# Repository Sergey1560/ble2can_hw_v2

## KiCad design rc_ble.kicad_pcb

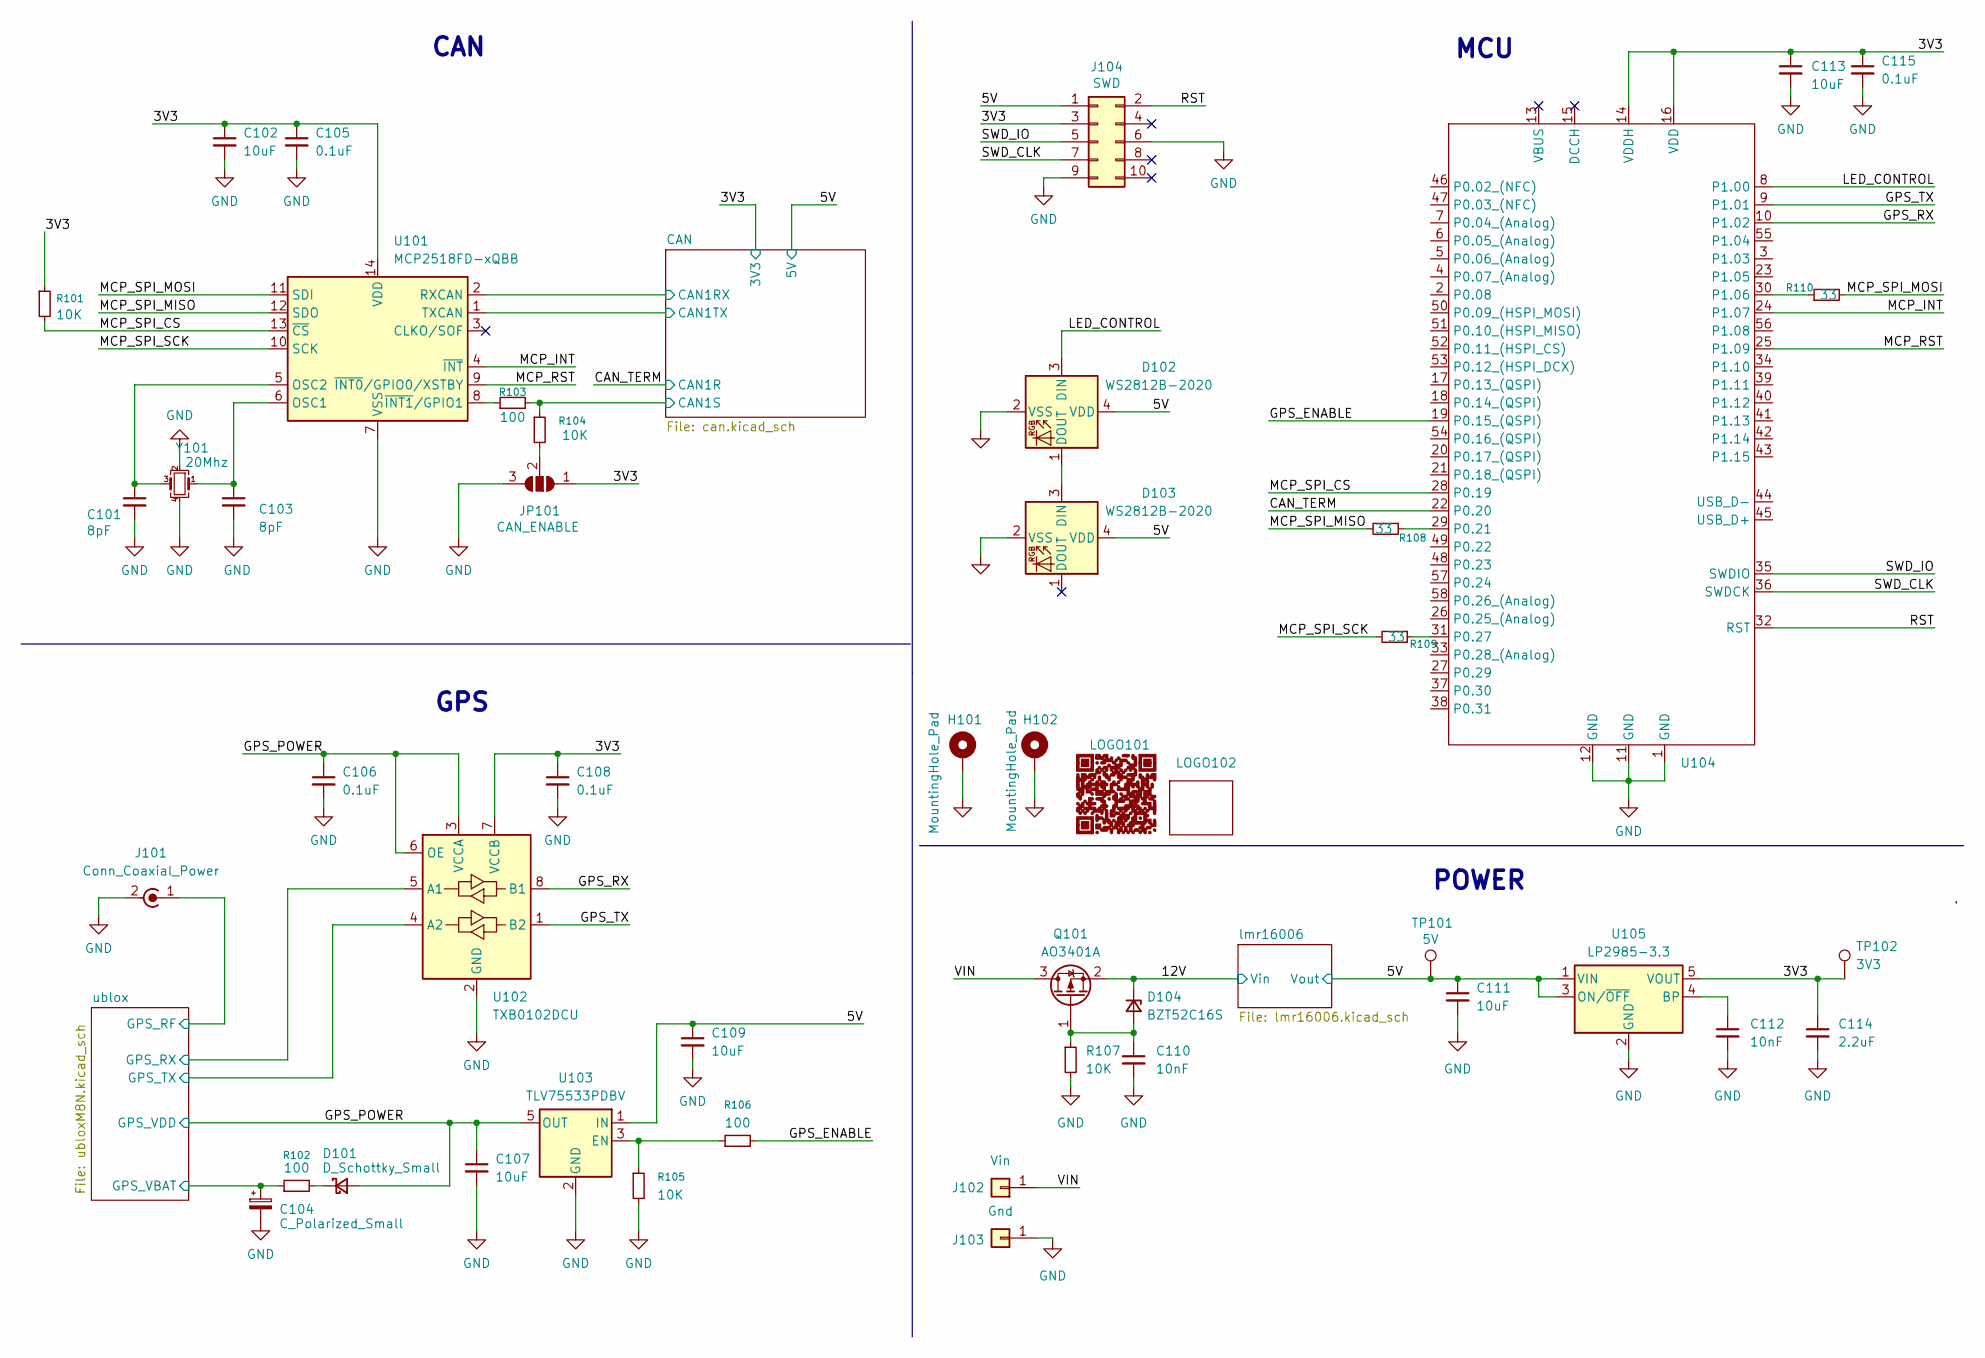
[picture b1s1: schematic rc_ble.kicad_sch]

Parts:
C101, C103: 8pF; C_0603_1608Metric; LCSC C38523
C102, C107, C109, C113: 10uF; C_0805_2012Metric
C104: C_Polarized_Small; CP_Radial_D8.0mm_P3.50mm
C105, C115: 0.1uF; C_0603_1608Metric
C106, C108: 0.1uF; C_0603_1608Metric; LCSC C14663
C110, C112: 10nF; C_0603_1608Metric; LCSC C57112
C111: 10uF; C_0603_1608Metric; LCSC C15849
C114: 2.2uF; C_0603_1608Metric; LCSC C23630
D101: D_Schottky_Small; D_SOD-323_HandSoldering
D102, D103: WS2812B-2020; LED_WS2812B-2020_PLCC4_2.0x2.0mm; LCSC C965555
D104: BZT52C16S; D_SOD-323_HandSoldering; LCSC C173447
H101, H102: MountingHole_Pad; MountingHole_2.2mm_M2_Pad_Via
J101: Conn_Coaxial_Power; SMA_Amphenol_132134_Vertical
J102: Vin; PinHeader_1x01_P2.54mm_Vertical
J103: Gnd; PinHeader_1x01_P2.54mm_Vertical
J104: SWD; PinHeader_2x05_P1.27mm_Vertical_SMD
JP101: CAN_ENABLE; SolderJumper-3_P1.3mm_Open_RoundedPad1.0x1.5mm
LOGO101: logo_github
LOGO102: logo_15x9
Q101: AO3401A; SOT-23; LCSC C15127
R101, R104, R105, R107: 10K; R_0603_1608Metric; LCSC C25804
R102, R103, R106: 100; R_0603_1608Metric
R108, R109, R110: 33; R_0603_1608Metric
TP101: 5V; TestPoint_Pad_1.0x1.0mm
TP102: 3V3; TestPoint_Pad_1.0x1.0mm
U101: MCP2518FD-xQBB; DFN-14-1EP_3x4.5mm_P0.65mm_EP1.65x4.25mm; LCSC C621395
U102: TXB0102DCU; VSSOP-8_2.3x2mm_P0.5mm; LCSC C60709
U103: TLV75533PDBV; SOT-23-5
U104: nrf5340
U105: LP2985-3.3; SOT-23-5; LCSC C95414
Y101: 20Mhz; Crystal_SMD_3225-4Pin_3.2x2.5mm

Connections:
/3V3: C102.1, C105.1, C108.1, C113.1, C114.1, C115.1, J104.3, JP101.1 (A), R101.1, TP102.1, U101.14 (VDD), U102.7 (VCCB), U104.14 (VDDH), U104.16 (VDD), U105.5 (VOUT); also elsewhere on the board
/5V: C109.1, C111.1, D102.4 (VDD), D103.4 (VDD), J104.1, TP101.1, U103.1 (IN), U105.1 (VIN), U105.3 (ON/~OFF); also elsewhere on the board
/12V: D104.1 (K), Q101.2 (S); also elsewhere on the board
/CAN/CAN1RX: U101.2 (RXCAN); also elsewhere on the board
/CAN/CAN1S: R103.2, R104.1; also elsewhere on the board
/CAN/CAN1TX: U101.1 (TXCAN); also elsewhere on the board
/CAN_TERM: U104.22 (P0.20); also elsewhere on the board
/GPS_ENABLE: R106.2, U104.19 (P0.15_(QSPI))
/GPS_POWER: C106.1, C107.1, D101.2 (A), U102.3 (VCCA), U102.6 (OE), U103.5 (OUT); also elsewhere on the board
/GPS_RX: U102.8 (B1), U104.10 (P1.02)
/GPS_TX: U102.1 (B2), U104.9 (P1.01)
/LED_CONTROL: D102.3 (DIN), U104.8 (P1.00)
/MCP_INT: U101.4 (~INT), U104.24 (P1.07)
/MCP_RST: U101.9 (~INT0/GPIO0/XSTBY), U104.25 (P1.09)
/MCP_SPI_CS: R101.2, U101.13 (~CS), U104.28 (P0.19)
/MCP_SPI_MISO: R108.2, U101.12 (SDO)
/MCP_SPI_MOSI: R110.2, U101.11 (SDI)
/MCP_SPI_SCK: R109.2, U101.10 (SCK)
/RST: J104.2, U104.32 (RST)
/SWD_CLK: J104.7, U104.36 (SWDCK)
/SWD_IO: J104.5, U104.35 (SWDIO)
/VIN: J102.1, Q101.3 (D)
/ublox/GPS_RF: J101.1 (In); also elsewhere on the board
/ublox/GPS_RX: U102.5 (A1); also elsewhere on the board
/ublox/GPS_TX: U102.4 (A2); also elsewhere on the board
/ublox/GPS_VBAT: C104.1, R102.1; also elsewhere on the board
GND: C101.2, C102.2, C103.2, C104.2, C105.2, C106.2, C107.2, C108.2, C109.2, C110.2, C111.2, C112.2, C113.2, C114.2, C115.2, D102.2 (VSS), D103.2 (VSS), H101.1, H102.1, J101.2 (Ext), J103.1, J104.6, J104.9, JP101.3 (B), R105.2, R107.2, U101.7 (VSS), U101.15 (VSS), U102.2 (GND), U103.2 (GND), U104.1 (GND), U104.11 (GND), U104.12 (GND), U105.2 (GND), Y101.2, Y101.4; also elsewhere on the board
unnamed: D101.1 (K), R102.2
unnamed: D102.1 (DOUT), D103.3 (DIN)
unnamed: C110.1, D104.2 (A), Q101.1 (G), R107.1
unnamed: JP101.2 (C), R104.2
unnamed: C103.1, U101.6 (OSC1), Y101.1
unnamed: C101.1, U101.5 (OSC2), Y101.3
unnamed: R103.1, U101.8 (~INT1/GPIO1)
unnamed: R105.1, R106.1, U103.3 (EN)
unnamed: R108.1, U104.29 (P0.21)
unnamed: R109.1, U104.31 (P0.27)
unnamed: R110.1, U104.30 (P1.06)
unnamed: C112.1, U105.4 (BP)

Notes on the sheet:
GPS
CAN
MCU
POWER

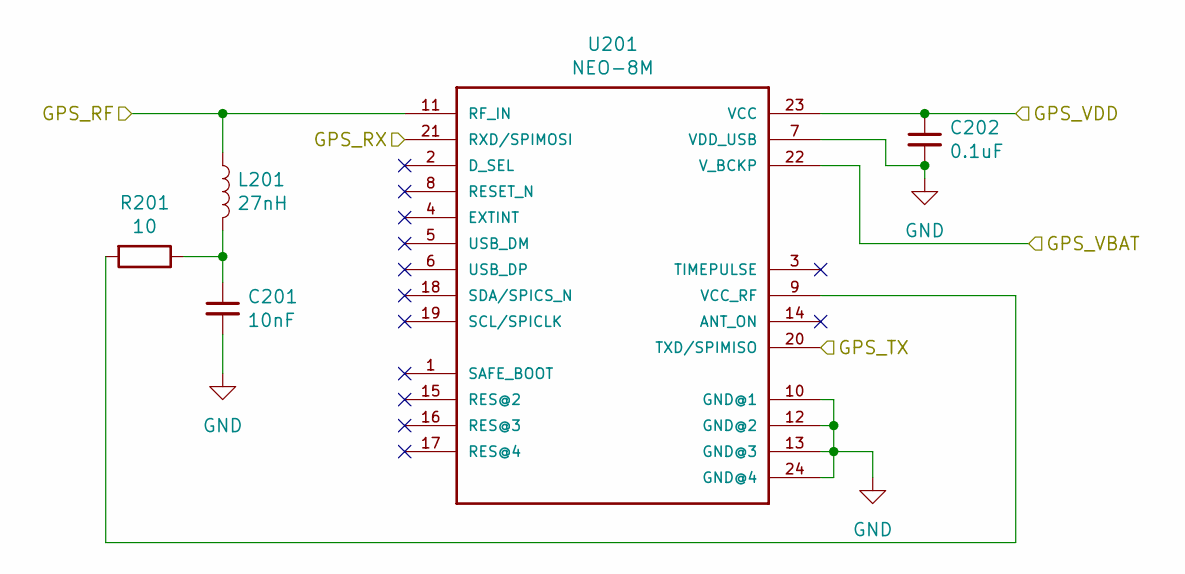
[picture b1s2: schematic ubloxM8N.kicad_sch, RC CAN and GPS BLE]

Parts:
C201: 10nF; C_0603_1608Metric
C202: 0.1uF; C_0805_2012Metric
L201: 27nH; L_0805_2012Metric
R201: 10; R_0603_1608Metric
U201: NEO-8M; ublox_NEO; LCSC C5119087

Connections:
/GPS_POWER: C202.1, U201.23 (VCC); also elsewhere on the board
/ublox/GPS_RF: L201.1, U201.11 (RF_IN); also elsewhere on the board
/ublox/GPS_RX: U201.21 (RXD/SPIMOSI); also elsewhere on the board
/ublox/GPS_TX: U201.20 (TXD/SPIMISO); also elsewhere on the board
/ublox/GPS_VBAT: U201.22 (V_BCKP); also elsewhere on the board
GND: C201.2, C202.2, U201.7 (VDD_USB), U201.10 (GND@1), U201.12 (GND@2), U201.13 (GND@3), U201.24 (GND@4); also elsewhere on the board
unnamed: C201.1, L201.2, R201.1
unnamed: R201.2, U201.9 (VCC_RF)

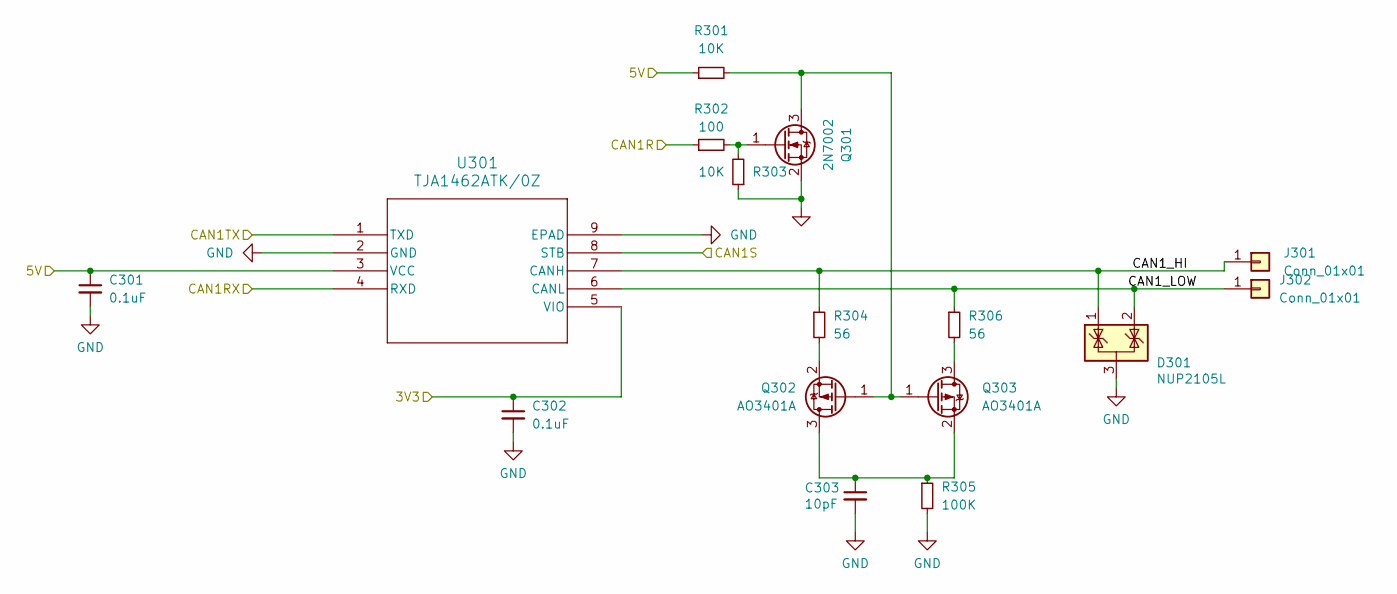
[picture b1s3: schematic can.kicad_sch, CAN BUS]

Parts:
C301, C302: 0.1uF; C_0603_1608Metric; LCSC C14663
C303: 10pF; C_0603_1608Metric; LCSC C1669
D301: NUP2105L; SOT-23; LCSC C284104
J301, J302: Conn_01x01; PinHeader_1x01_P2.54mm_Vertical
Q301: 2N7002; SOT-23; LCSC C8545
Q302, Q303: AO3401A; SOT-23; LCSC C15127
R301, R303: 10K; R_0603_1608Metric; LCSC C25804
R302: 100; R_0603_1608Metric; LCSC C22775
R304, R306: 56; R_0603_1608Metric; LCSC C25196
R305: 100K; R_0603_1608Metric; LCSC C25803
U301: TJA1462ATK/0Z; HVSON8_TJA1462_NXP; LCSC C3229259

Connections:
/3V3: C302.1, U301.5 (VIO); also elsewhere on the board
/5V: C301.1, R301.1, U301.3 (VCC); also elsewhere on the board
/CAN/CAN1RX: U301.4 (RXD); also elsewhere on the board
/CAN/CAN1S: U301.8 (STB); also elsewhere on the board
/CAN/CAN1TX: U301.1 (TXD); also elsewhere on the board
/CAN/CAN1_HI: D301.1 (K), J301.1, R304.1, U301.7 (CANH)
/CAN/CAN1_LOW: D301.2 (K), J302.1, R306.1, U301.6 (CANL)
/CAN_TERM: R302.1; also elsewhere on the board
GND: C301.2, C302.2, C303.2, D301.3 (A), Q301.2 (S), R303.1, R305.2, U301.2 (GND), U301.9 (EPAD); also elsewhere on the board
unnamed: Q301.3 (D), Q302.1 (G), Q303.1 (G), R301.2
unnamed: Q301.1 (G), R302.2, R303.2
unnamed: C303.1, Q302.3 (D), Q303.2 (S), R305.1
unnamed: Q302.2 (S), R304.2
unnamed: Q303.3 (D), R306.2

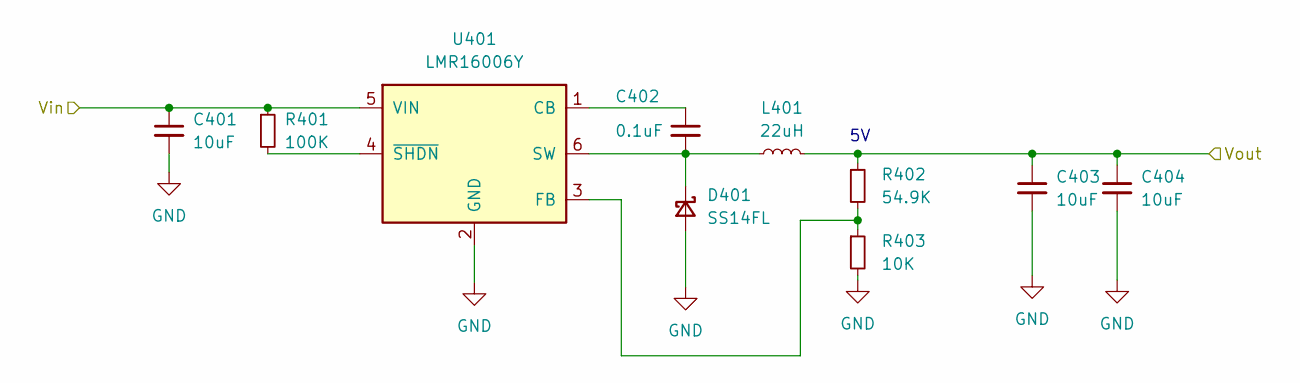
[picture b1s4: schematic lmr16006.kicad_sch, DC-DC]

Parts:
C401, C403, C404: 10uF; C_0805_2012Metric; LCSC C440198
C402: 0.1uF; C_0805_2012Metric; LCSC C28233
D401: SS14FL; D_SMA; LCSC C111580
L401: 22uH; FNR5040S220MT; LCSC C167971
R401: 100K; R_0603_1608Metric; LCSC C25803
R402: 54.9K; R_0603_1608Metric; LCSC C728593
R403: 10K; R_0603_1608Metric; LCSC C25804
U401: LMR16006Y; SOT-23-6; LCSC C290195

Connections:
/5V: C403.1, C404.1, L401.2, R402.1; also elsewhere on the board
/12V: C401.1, R401.1, U401.5 (VIN); also elsewhere on the board
GND: C401.2, C403.2, C404.2, D401.2 (A), R403.2, U401.2 (GND); also elsewhere on the board
unnamed: C402.2, D401.1 (K), L401.1, U401.6 (SW)
unnamed: C402.1, U401.1 (CB)
unnamed: R402.2, R403.1, U401.3 (FB)
unnamed: R401.2, U401.4 (~SHDN)

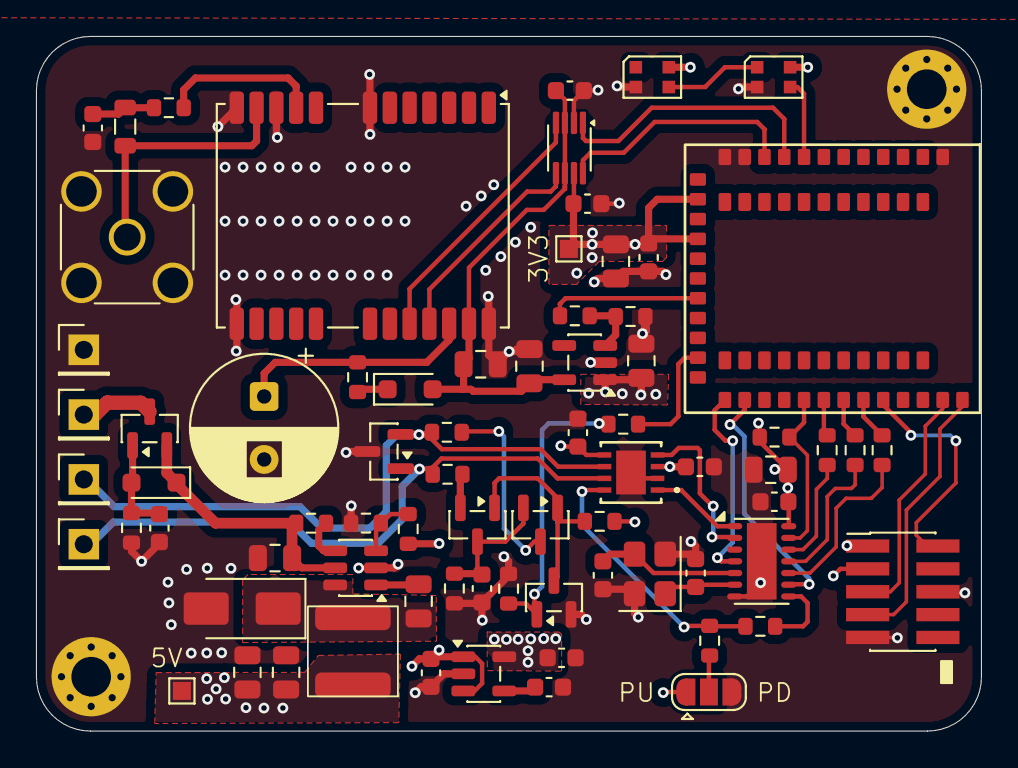
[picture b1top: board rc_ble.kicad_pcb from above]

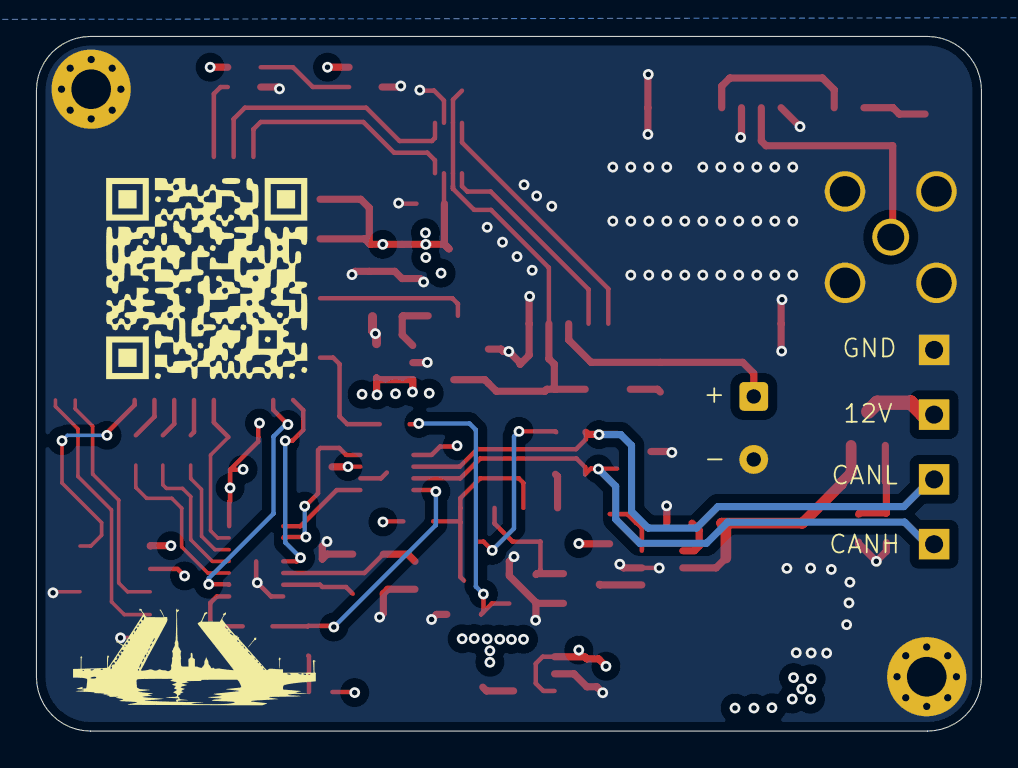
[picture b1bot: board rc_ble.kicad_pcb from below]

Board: 4 copper layers, 52.5 x 38.6 mm, 78 parts (2 on the bottom side), 52 nets.

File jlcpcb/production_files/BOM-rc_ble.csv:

Comment,Designator,Footprint,LCSC,Quantity
0.1uF,"C105,C106,C108,C115,C301,C302",C_0603_1608Metric,C14663,6
0.1uF,"C202,C402",C_0805_2012Metric,C28233,2
10,R201,R_0603_1608Metric,C22859,1
100,"R102,R103,R106,R302",R_0603_1608Metric,C22775,4
100K,"R305,R401",R_0603_1608Metric,C25803,2
10K,"R101,R104,R105,R107,R301,R303,R403",R_0603_1608Metric,C25804,7
10nF,"C110,C112,C201",C_0603_1608Metric,C57112,3
10pF,C303,C_0603_1608Metric,C1634,1
10uF,C111,C_0603_1608Metric,C15849,1
10uF,"C102,C107,C109,C113,C401,C403,C404",C_0805_2012Metric,C440198,7
2.2uF,C114,C_0603_1608Metric,C23630,1
20Mhz,Y101,Crystal_SMD_3225-4Pin_3.2x2.5mm,C481408,1
22uH,L401,FNR5040S220MT,C167971,1
27nH,L201,L_0805_2012Metric,C964068,1
2N7002,Q301,SOT-23,C8545,1
33,"R108,R109,R110",R_0603_1608Metric,C23140,3
54.9K,R402,R_0603_1608Metric,C728593,1
56,"R304,R306",R_0603_1608Metric,C25196,2
8pF,"C101,C103",C_0603_1608Metric,C36508,2
AO3401A,"Q101,Q302,Q303",SOT-23,C15127,3
BZT52C16S,D104,D_SOD-323_HandSoldering,C173447,1
D_Schottky_Small,D101,D_SOD-323_HandSoldering,C191023,1
LMR16006Y,U401,SOT-23-6,C290195,1
LP2985-3.3,U105,SOT-23-5,C95414,1
MCP2518FD-xQBB,U101,DFN-14-1EP_3x4.5mm_P0.65mm_EP1.65x4.25mm,C621395,1
NEO-8M,U201,ublox_NEO,C5119087,1
NUP2105L,D301,SOT-23,C284104,1
SS14FL,D401,D_SMA,C111580,1
SWD,J104,PinHeader_2x05_P1.27mm_Vertical_SMD,C42372555,1
TJA1462ATK/0Z,U301,HVSON8_TJA1462_NXP,C3229259,1
TLV75533PDBV,U103,SOT-23-5,C404027,1
TXB0102DCU,U102,VSSOP-8_2.3x2mm_P0.5mm,C60709,1
WS2812B-2020,"D102,D103",LED_WS2812B-2020_PLCC4_2.0x2.0mm,C965555,2

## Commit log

2025-08-31 holyiot module
2025-12-26 redesing board
2025-12-29 VDDH pin
2025-12-29 PCBA ready
